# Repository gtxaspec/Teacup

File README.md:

# TLDR: Where do i get one?
Stay Tuned!

# Teacup-Rev-C
Teacup T31 development board

Tested config as follows:

## Operating System: Thingino

## Video: Camera sensor Sony IMX327 confirmed working with 15pin PiCam module. 
```https://www.amazon.com/dp/B085VLS96S```

To initialize the camera sensor on boot issue the following command.
```fw_setenv sensor imx327``` 
This will set the sensor in the uboot environment and start the sensor on boot 

## Networking:
```https://www.amazon.com/dp/B00MYT481C```

Asix USB 2.0 ethernet adapter. This adapter works in both uboot and userland.
GMAC PHY also pinned out to a header for use with an external phy.

## Audio
Audio out and Mic tested and work

## Firmware
Thingino firmware, code is available on their Github
https://github.com/themactep/thingino-firmware/wiki

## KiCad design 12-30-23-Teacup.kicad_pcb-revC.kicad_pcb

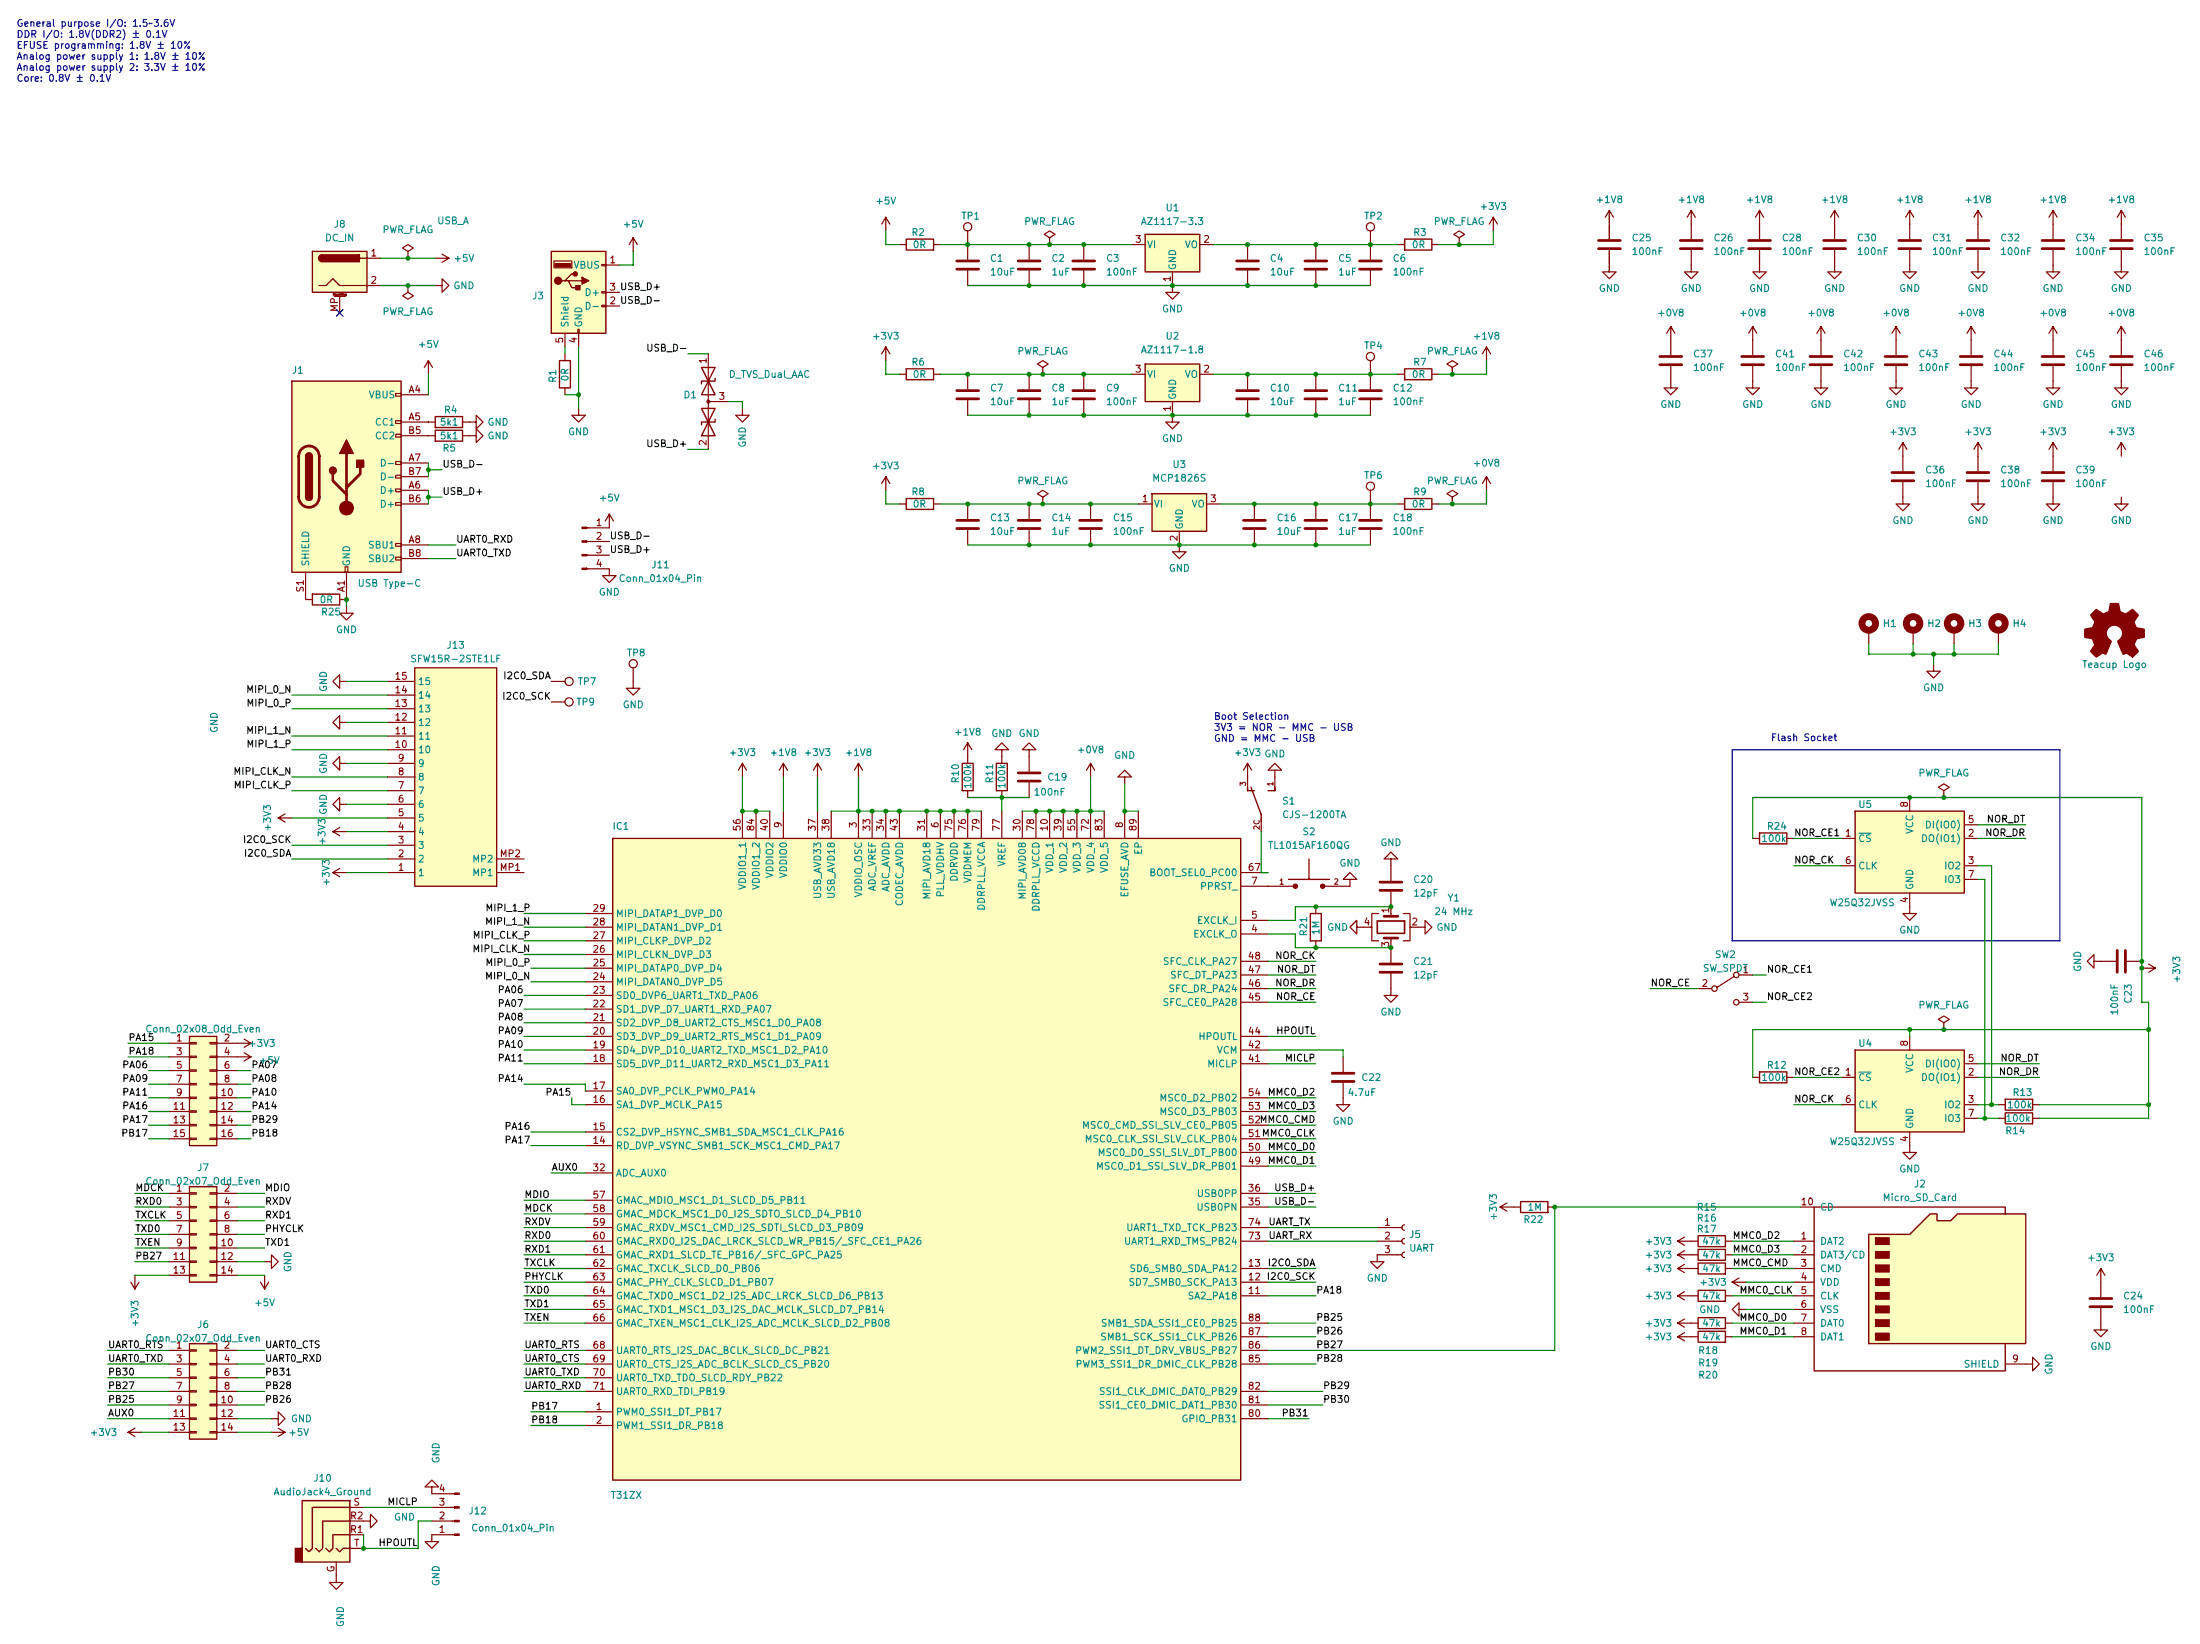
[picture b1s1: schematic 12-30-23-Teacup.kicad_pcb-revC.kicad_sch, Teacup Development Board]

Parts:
C1, C4, C7, C10, C13, C16: 10uF; C_0805_2012Metric_Pad1.18x1.45mm_HandSolder
C2, C5, C8, C11, C14, C17: 1uF; C_0603_1608Metric_Pad1.08x0.95mm_HandSolder
C3, C6, C9, C12, C15, C18, C19: 100nF; C_0603_1608Metric_Pad1.08x0.95mm_HandSolder
C20, C21: 12pF; C_0402_1005Metric
C22: 4.7uF; C_0603_1608Metric_Pad1.08x0.95mm_HandSolder
C23, C24, C25, C26, C28, C30, C31, C32, C34, C35, C36, C37, C38, C39, C41, C42, C43, C44, C45, C46: 100nF; C_0402_1005Metric
D1: D_TVS_Dual_AAC; SOT-23-3; Manufacturer Part Number PESD5V0U2BT,215
H1, H2, H3, H4: MountingHole_Pad; MountingHole_2.7mm_M2.5_Pad_Via
IC1: T31ZX; QFN35P900X900X90-89N-D; Mouser Part Number 870-T31ZX
J1: USB Type-C; USB_C_Receptacle_HRO_TYPE-C-31-M-12; Manufacturer Part Number TYPE-C-31-M-12 (USB4105-GF-A)
J2: Micro_SD_Card; microSD_HC_Hirose_DM3D-SF
J3: USB_A; USB_A_TE_292303-7_Horizontal
J4: Conn_02x08_Odd_Even; PinHeader_2x08_P2.54mm_Vertical
J5: UART; PinHeader_1x03_P2.54mm_Vertical
J6, J7: Conn_02x07_Odd_Even; PinHeader_2x07_P2.54mm_Vertical
J8: DC_IN; BarrelJack_Wuerth_6941xx301002
J10: AudioJack4_Ground; Jack_3.5mm_PJ320D_Horizontal
J11, J12: Conn_01x04_Pin; PinHeader_1x04_P2.54mm_Vertical
J13: SFW15R-2STE1LF; SFW15R2STE1LF; Mouser Part Number 649-SFW15R-2STE1LF
LOGO1: Teacup Logo; Teacup-logo
R1, R2, R3, R6, R7, R8, R9, R25: 0R; R_0603_1608Metric_Pad0.98x0.95mm_HandSolder
R4, R5: 5k1; R_0603_1608Metric_Pad0.98x0.95mm_HandSolder
R10, R11, R12, R13, R14, R24: 100k; R_0603_1608Metric_Pad0.98x0.95mm_HandSolder
R15, R16, R17, R18, R19, R20: 47k; R_0603_1608Metric_Pad0.98x0.95mm_HandSolder
R21, R22: 1M; R_0402_1005Metric
S1: CJS-1200TA
S2: TL1015AF160QG; SW_TL1015AF160QG; PARTREV F
SW2: SW_SPDT; SW_SPDT_CK-JS102011SAQN
TP1, TP2, TP4, TP6, TP7, TP8, TP9: TestPoint; TestPoint_Pad_D1.5mm
U1: AZ1117-3.3; SOT-223-3_TabPin2; Manufacturer Part Number AZ1117IH-3.3TRG1
U2: AZ1117-1.8; SOT-223-3_TabPin2; Manufacturer Part Number AZ1117(CH)-1.8
U3: MCP1826S; SOT-223-3_TabPin2; Manufacturer Part Number MCP1826S
U4: W25Q32JVSS; SOIC-8_5.23x5.23mm_P1.27mm; Manufacturer Part Number W25Q32JVSS
U5: W25Q32JVSS; DIP-8_W7.62mm_Socket_LongPads
Y1: 24 MHz; Crystal_SMD_2016-4Pin_2.0x1.6mm; Manufacturer Part Number NX2016SA-24MHZ-EXS00A-CS07553

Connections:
+0V8: C37.1, C41.1, C42.1, C43.1, C44.1, C45.1, C46.1, IC1.10 (VDD_1), IC1.30 (MIPI_AVD08), IC1.39 (VDD_2), IC1.55 (VDD_3), IC1.72 (VDD_4), IC1.78 (DDRPLL_VCCD), IC1.83 (VDD_5), R9.1
+1V8: C25.1, C26.1, C28.1, C30.1, C31.1, C32.1, C34.1, C35.1, IC1.3 (VDDIO_OSC), IC1.6 (PLL_VDDHV), IC1.9 (VDDIO0), IC1.31 (MIPI_AVD18), IC1.33 (ADC_VREF), IC1.34 (ADC_AVDD), IC1.38 (USB_AVD18), IC1.43 (CODEC_AVDD), IC1.75 (DDRVDD), IC1.76 (VDDMEM), IC1.79 (DDRPLL_VCCA), R7.1, R10.1
+3V3: C23.1, C24.1, C36.1, C38.1, C39.1, IC1.37 (USB_AVD33), IC1.40 (VDDIO2), IC1.56 (VDDIO1_1), IC1.84 (VDDIO1_2), J2.4 (VDD), J4.2, J6.13, J7.13, J13.1, J13.4, J13.5, R3.1, R6.1, R8.1, R12.2, R13.1, R14.2, R15.1, R16.1, R17.1, R18.1, R19.1, R20.1, R22.1, R24.2, S1.3, U4.8 (VCC), U5.8 (VCC)
+5V: J1.A4 (VBUS), J1.A9 (VBUS), J1.B4 (VBUS), J1.B9 (VBUS), J3.1 (VBUS), J4.4, J6.14, J7.14, J8.1, J11.1, R2.1
/AUX0: IC1.32 (ADC_AUX0), J6.11
/HPOUTL: IC1.44 (HPOUTL), J10.R1, J10.T, J12.2
/I2C0_SCK: IC1.12 (SD7_SMB0_SCK_PA13), J13.3, TP9.1
/I2C0_SDA: IC1.13 (SD6_SMB0_SDA_PA12), J13.2, TP7.1
/MDCK: IC1.58 (GMAC_MDCK_MSC1_D0_I2S_SDTO_SLCD_D4_PB10), J7.1
/MDIO: IC1.57 (GMAC_MDIO_MSC1_D1_SLCD_D5_PB11), J7.2
/MICLP: IC1.41 (MICLP), J10.S, J12.3
/MIPI_0_N: IC1.24 (MIPI_DATAN0_DVP_D5), J13.14
/MIPI_0_P: IC1.25 (MIPI_DATAP0_DVP_D4), J13.13
/MIPI_1_N: IC1.28 (MIPI_DATAN1_DVP_D1), J13.11
/MIPI_1_P: IC1.29 (MIPI_DATAP1_DVP_D0), J13.10
/MIPI_CLK_N: IC1.26 (MIPI_CLKN_DVP_D3), J13.8
/MIPI_CLK_P: IC1.27 (MIPI_CLKP_DVP_D2), J13.7
/MMC0_CLK: IC1.51 (MSC0_CLK_SSI_SLV_CLK_PB04), J2.5 (CLK), R18.2
/MMC0_CMD: IC1.52 (MSC0_CMD_SSI_SLV_CE0_PB05), J2.3 (CMD), R17.2
/MMC0_D0: IC1.50 (MSC0_D0_SSI_SLV_DT_PB00), J2.7 (DAT0), R19.2
/MMC0_D1: IC1.49 (MSC0_D1_SSI_SLV_DR_PB01), J2.8 (DAT1), R20.2
/MMC0_D2: IC1.54 (MSC0_D2_PB02), J2.1 (DAT2), R15.2
/MMC0_D3: IC1.53 (MSC0_D3_PB03), J2.2 (DAT3/CD), R16.2
/NOR_CE: IC1.45 (SFC_CE0_PA28), SW2.2 (B)
/NOR_CE1: R24.1, SW2.1 (A), U5.1 (~CS)
/NOR_CE2: R12.1, SW2.3 (C), U4.1 (~CS)
/NOR_CK: IC1.48 (SFC_CLK_PA27), U4.6 (CLK), U5.6 (CLK)
/NOR_DR: IC1.46 (SFC_DR_PA24), U4.2 (DO(IO1)), U5.2 (DO(IO1))
/NOR_DT: IC1.47 (SFC_DT_PA23), U4.5 (DI(IO0)), U5.5 (DI(IO0))
/PA06: IC1.23 (SD0_DVP6_UART1_TXD_PA06), J4.5
/PA07: IC1.22 (SD1_DVP_D7_UART1_RXD_PA07), J4.6
/PA08: IC1.21 (SD2_DVP_D8_UART2_CTS_MSC1_D0_PA08), J4.8
/PA09: IC1.20 (SD3_DVP_D9_UART2_RTS_MSC1_D1_PA09), J4.7
/PA10: IC1.19 (SD4_DVP_D10_UART2_TXD_MSC1_D2_PA10), J4.10
/PA11: IC1.18 (SD5_DVP_D11_UART2_RXD_MSC1_D3_PA11), J4.9
/PA14: IC1.17 (SA0_DVP_PCLK_PWM0_PA14), J4.12
/PA15: IC1.16 (SA1_DVP_MCLK_PA15), J4.1
/PA16: IC1.15 (CS2_DVP_HSYNC_SMB1_SDA_MSC1_CLK_PA16), J4.11
/PA17: IC1.14 (RD_DVP_VSYNC_SMB1_SCK_MSC1_CMD_PA17), J4.13
/PA18: IC1.11 (SA2_PA18), J4.3
/PB17: IC1.1 (PWM0_SSI1_DT_PB17), J4.15
/PB18: IC1.2 (PWM1_SSI1_DR_PB18), J4.16
/PB25: IC1.88 (SMB1_SDA_SSI1_CE0_PB25), J6.9
/PB26: IC1.87 (SMB1_SCK_SSI1_CLK_PB26), J6.10
/PB27: IC1.86 (PWM2_SSI1_DT_DRV_VBUS_PB27), J2.10 (CD), J6.7, J7.11, R22.2
/PB28: IC1.85 (PWM3_SSI1_DR_DMIC_CLK_PB28), J6.8
/PB29: IC1.82 (SSI1_CLK_DMIC_DAT0_PB29), J4.14
/PB30: IC1.81 (SSI1_CE0_DMIC_DAT1_PB30), J6.5
/PB31: IC1.80 (GPIO_PB31), J6.6
/PHYCLK: IC1.63 (GMAC_PHY_CLK_SLCD_D1_PB07), J7.8
/RXD0: IC1.60 (GMAC_RXD0_I2S_DAC_LRCK_SLCD_WR_PB15/_SF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), J7.3
/RXD1: IC1.61 (GMAC_RXD1_SLCD_TE_PB16/_SFC_GPC_PA25), J7.6
/RXDV: IC1.59 (GMAC_RXDV_MSC1_CMD_I2S_SDTI_SLCD_D3_PB09), J7.4
/TXCLK: IC1.62 (GMAC_TXCLK_SLCD_D0_PB06), J7.5
/TXD0: IC1.64 (GMAC_TXD0_MSC1_D2_I2S_ADC_LRCK_SLCD_D6_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), J7.7
/TXD1: IC1.65 (GMAC_TXD1_MSC1_D3_I2S_DAC_MCLK_SLCD_D7_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), J7.10
/TXEN: IC1.66 (GMAC_TXEN_MSC1_CLK_I2S_ADC_MCLK_SLCD_D2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), J7.9
/UART0_CTS: IC1.69 (UART0_CTS_I2S_ADC_BCLK_SLCD_CS_PB20), J6.2
/UART0_RTS: IC1.68 (UART0_RTS_I2S_DAC_BCLK_SLCD_DC_PB21), J6.1
/UART0_RXD: IC1.71 (UART0_RXD_TDI_PB19), J1.A8 (SBU1), J6.4
/UART0_TXD: IC1.70 (UART0_TXD_TDO_SLCD_RDY_PB22), J1.B8 (SBU2), J6.3
/UART_RX: IC1.73 (UART1_RXD_TMS_PB24), J5.2
/UART_TX: IC1.74 (UART1_TXD_TCK_PB23), J5.1
/USB_D+: D1.2 (A2), IC1.36 (USB0PP), J1.A6 (D+), J1.B6 (D+), J3.3 (D+), J11.3
/USB_D-: D1.1 (A1), IC1.35 (USB0PN), J1.A7 (D-), J1.B7 (D-), J3.2 (D-), J11.2
GND: C1.2, C2.2, C3.2, C4.2, C5.2, C6.2, C7.2, C8.2, C9.2, C10.2, C11.2, C12.2, C13.2, C14.2, C15.2, C16.2, C17.2, C18.2, C19.1, C20.1, C21.2, C22.2, C23.2, C24.2, C25.2, C26.2, C28.2, C30.2, C31.2, C32.2, C34.2, C35.2, C36.2, C37.2, C38.2, C39.2, C41.2, C42.2, C43.2, C44.2, C45.2, C46.2, D1.3 (common), H1.1, H2.1, H3.1, H4.1, IC1.8 (EFUSE_AVD), IC1.89 (EP), J1.A1 (GND), J1.A12 (GND), J1.B1 (GND), J1.B12 (GND), J2.6 (VSS), J2.9 (SHIELD), J3.4 (GND), J5.3, J6.12, J7.12, J8.2, J10.G, J10.R2, J11.4, J12.1, J12.4, J13.6, J13.9, J13.12, J13.15, R1.1, R4.1, R5.1, R11.1, R25.1, S1.1, S2.2, TP8.1, U1.1 (GND), U2.1 (GND), U3.2 (GND), U4.4 (GND), U5.4 (GND), Y1.2, Y1.4
unnamed: IC1.67 (BOOT_SEL0_PC00), S1.2C
unnamed: C20.2, IC1.5 (EXCLK_I), R21.1, Y1.1
unnamed: C21.1, IC1.4 (EXCLK_O), R21.2, Y1.3
unnamed: IC1.7 (PPRST_), S2.1
unnamed: C22.1, IC1.42 (VCM)
unnamed: C19.2, IC1.77 (VREF), R10.2, R11.2
unnamed: J1.A5 (CC1), R4.2
unnamed: J1.B5 (CC2), R5.2
unnamed: J1.S1 (SHIELD), R25.2
unnamed: J3.5 (Shield), R1.2
unnamed: C1.1, C2.1, C3.1, R2.2, TP1.1, U1.3 (VI)
unnamed: C4.1, C5.1, C6.1, R3.2, TP2.1, U1.2 (VO)
unnamed: C7.1, C8.1, C9.1, R6.2, U2.3 (VI)
unnamed: C10.1, C11.1, C12.1, R7.2, TP4.1, U2.2 (VO)
unnamed: C13.1, C14.1, C15.1, R8.2, U3.1 (VI)
unnamed: C16.1, C17.1, C18.1, R9.2, TP6.1, U3.3 (VO)
unnamed: R13.2, U4.3 (IO2), U5.3 (IO2)
unnamed: R14.1, U4.7 (IO3), U5.7 (IO3)

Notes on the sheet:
Boot Selection 3V3 = NOR - MMC - USB GND = MMC - USB
Flash Socket
General purpose I/O: 1.5~3.6V DDR I/O: 1.8V(DDR2) ± 0.1V EFUSE programming: 1.8V ± 10% Analog power supply 1: 1.8V ± 10% Analog power supply 2: 3.3V ± 10% Core: 0.8V ± 0.1V

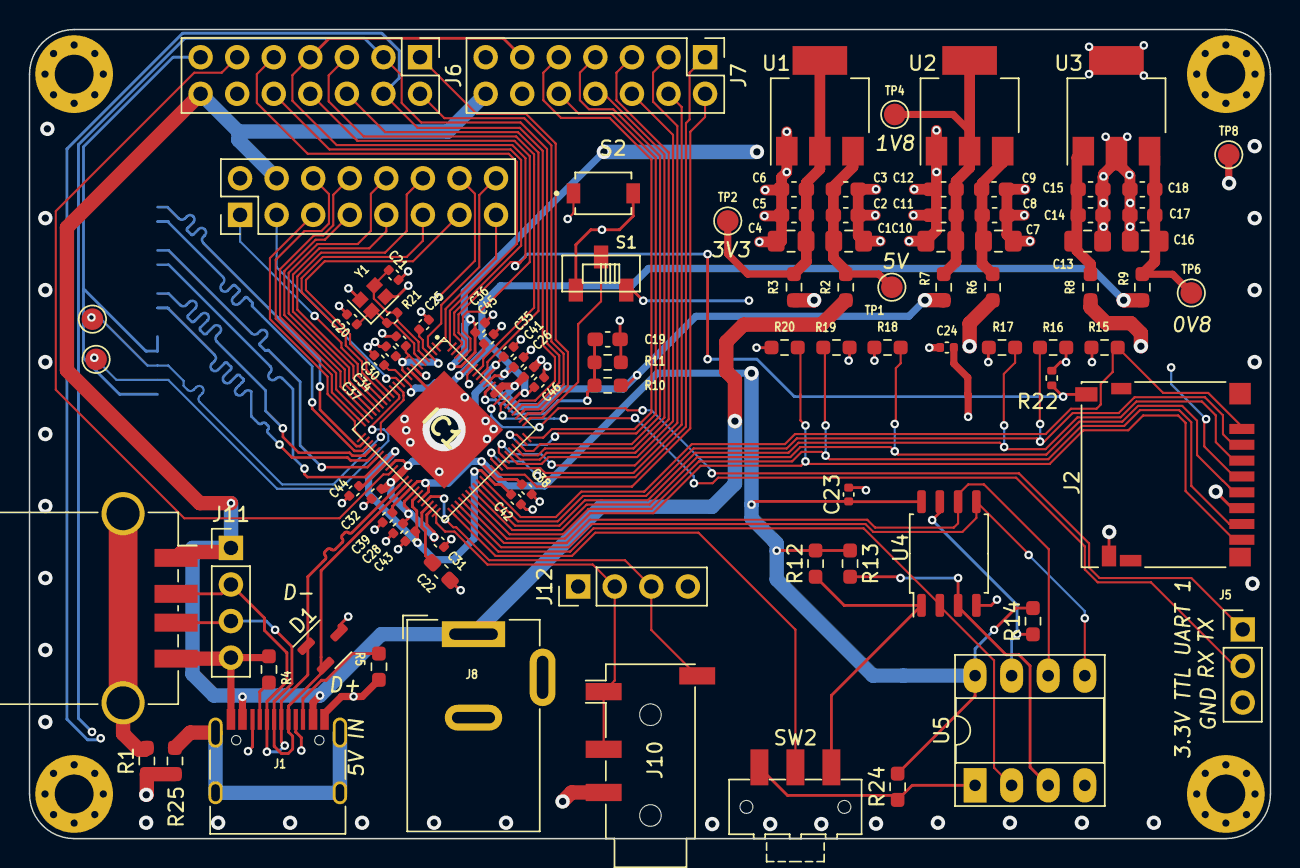
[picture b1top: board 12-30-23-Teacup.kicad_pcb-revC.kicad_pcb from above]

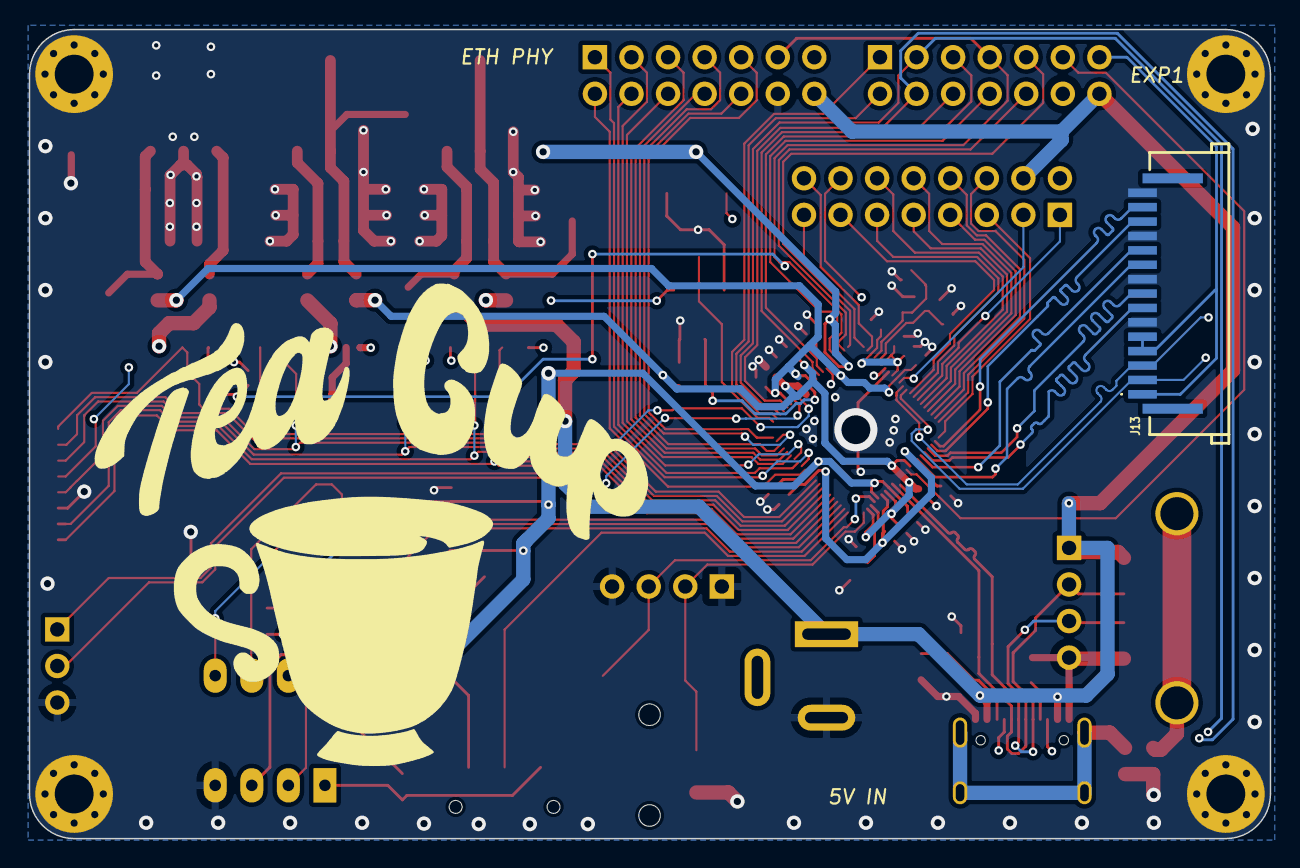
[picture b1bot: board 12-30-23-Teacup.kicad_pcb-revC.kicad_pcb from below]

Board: 4 copper layers, 86.2 x 56.2 mm, 101 parts (2 on the bottom side), 84 nets.

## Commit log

2024-01-20 Initial Commit
    Rev-C Ingenic T31 dev board
2024-01-22 Update 12-30-23-Teacup.kicad_pcb-revC.kicad_sch
    Update schematic
2024-01-22 Added R22 pullup resistor on PB27 to help the card detect recognition on the SD card
    Added R22 pullup resistor on PB27 to help the card detect recognition on the SD card
2024-01-23 Update silkscreen labels, add solder jumper for sensor enable
    Update silkscreen labels, add solder jumper for sensor enable
2024-01-23 Add silkscreen for bootsel and reset switches
2024-01-23 Correct typo in silk screen dc barrel jack
2024-01-23 Changed font on back silkscreen
2024-01-23 Add 3D render
2024-01-24 updated manufacturing gerber files
2024-02-21 Add Rev(C) 3.3
2024-02-21 README Update
2024-02-21 update silk
2024-02-21 Adjust silk
2024-02-21 update gerbers and bom
2024-02-21 update BOM
2024-02-21 silk
2024-03-05 Added bom and centroid position file for turnkey PCBWAY
2024-03-05 Update README.md
    Added link for PCBWWAY turnkey service
2024-03-06 included LCSC parts in BOM
2024-03-08 added jlcpcb manufacturing files
2024-03-18 Update README.md
    removed pcbway turnkey
2024-04-01 Update README.md
    Add Thingino Firmware link
2024-04-06 Update README.md
    spelling
2024-04-17 Update README.md
    Update turnkey info
